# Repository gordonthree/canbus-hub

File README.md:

# CAN bus hub prototype

## CAN Hub
* eight total de9 connectors, one input, one output, six spurs
* each spur is wired in series, with Cx-IN and Cx-OUT daisy chained
* spurs that are not connected have a shorting plug installed connecting Cx-IN to Cx-OUT

## CAN Hub using pin-terminals
* six 6-position terminals wired in series
* each spur is wired in series, with Cx-IN and Cx-OUT daisy chained
* bus-power LED
* +12v and ground wired in parallel

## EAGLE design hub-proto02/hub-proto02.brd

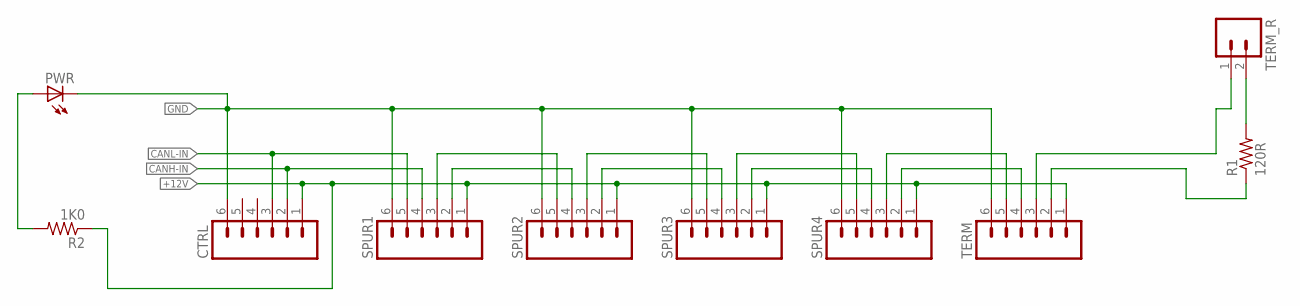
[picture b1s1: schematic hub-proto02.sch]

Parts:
CTRL: M06; 06P
PWR: LED3MM
R1: 120R; 0309/12
R2: 1K0; 0309/12
SPUR1, SPUR2, SPUR3, SPUR4: M06; 06P
TERM: M06; 06P
TERM_R: M02; 02P

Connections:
+12V: CTRL.1, R2.1, SPUR1.1, SPUR2.1, SPUR3.1, SPUR4.1, TERM.1
CANH-IN: CTRL.2, SPUR1.4
CANH-OUT: R1.1, TERM.2
CANL-IN: CTRL.3, SPUR1.5
CANL-OUT: TERM.3, TERM_R.1
GND: CTRL.6, PWR.K (C), SPUR1.6, SPUR2.6, SPUR3.6, SPUR4.6, TERM.6
unnamed: R1.2, TERM_R.2
unnamed: SPUR1.2, SPUR2.4
unnamed: SPUR1.3, SPUR2.5
unnamed: SPUR4.2, TERM.4
unnamed: SPUR4.3, TERM.5
unnamed: SPUR2.3, SPUR3.5
unnamed: SPUR2.2, SPUR3.4
unnamed: SPUR3.3, SPUR4.5
unnamed: SPUR3.2, SPUR4.4
unnamed: PWR.A, R2.2

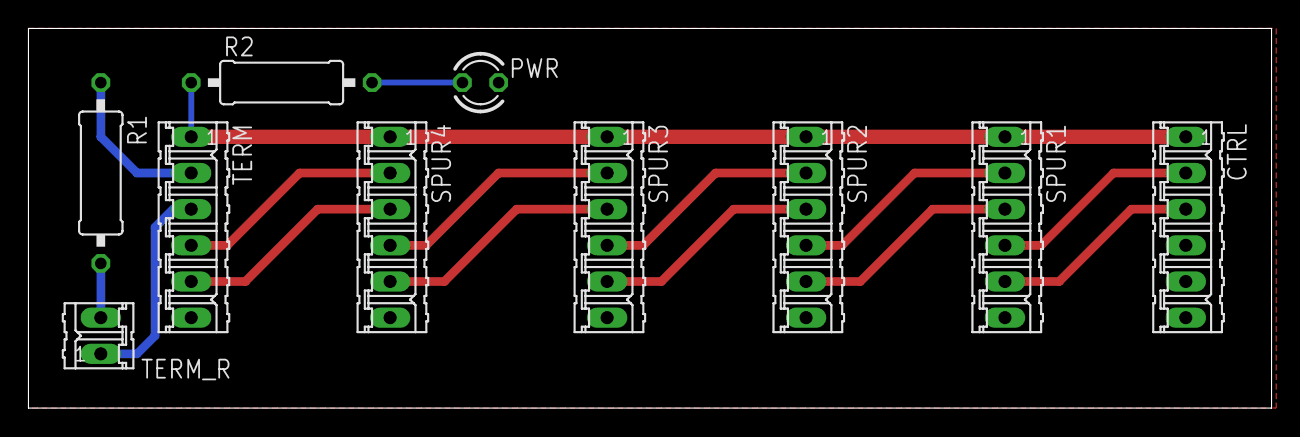
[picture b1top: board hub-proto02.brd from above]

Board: 2 copper layers, 87.3 x 26.7 mm, 10 parts (0 on the bottom side), 16 nets.

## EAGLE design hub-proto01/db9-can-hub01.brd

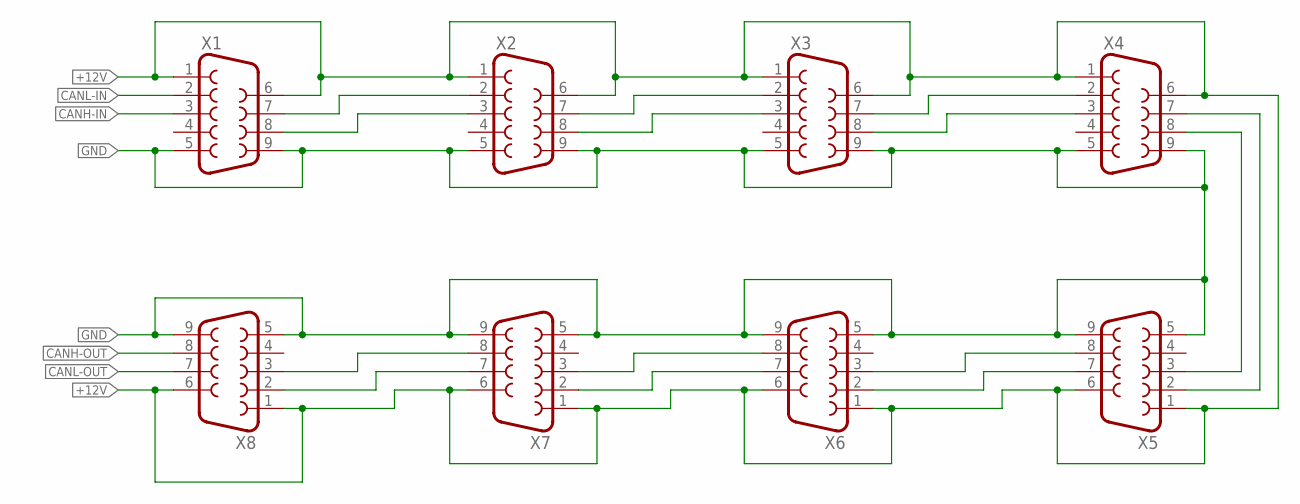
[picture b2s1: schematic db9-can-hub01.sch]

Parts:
X1, X2, X3, X4, X5, X6, X7, X8: F09H

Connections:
+12V: X1.1, X1.6, X2.1, X2.6, X3.1, X3.6, X4.1, X4.6, X5.1, X5.6, X6.1, X6.6, X7.1, X7.6, X8.1, X8.6
CANH-IN: X1.3
CANH-OUT: X8.8
CANL-IN: X1.2
CANL-OUT: X8.7
GND: X1.5, X1.9, X2.5, X2.9, X3.5, X3.9, X4.5, X4.9, X5.5, X5.9, X6.5, X6.9, X7.5, X7.9, X8.5, X8.9
unnamed: X1.7, X2.2
unnamed: X1.8, X2.3
unnamed: X2.7, X3.2
unnamed: X2.8, X3.3
unnamed: X3.7, X4.2
unnamed: X3.8, X4.3
unnamed: X4.8, X5.3
unnamed: X4.7, X5.2
unnamed: X5.7, X6.2
unnamed: X5.8, X6.3
unnamed: X6.7, X7.2
unnamed: X6.8, X7.3
unnamed: X7.7, X8.2
unnamed: X7.8, X8.3

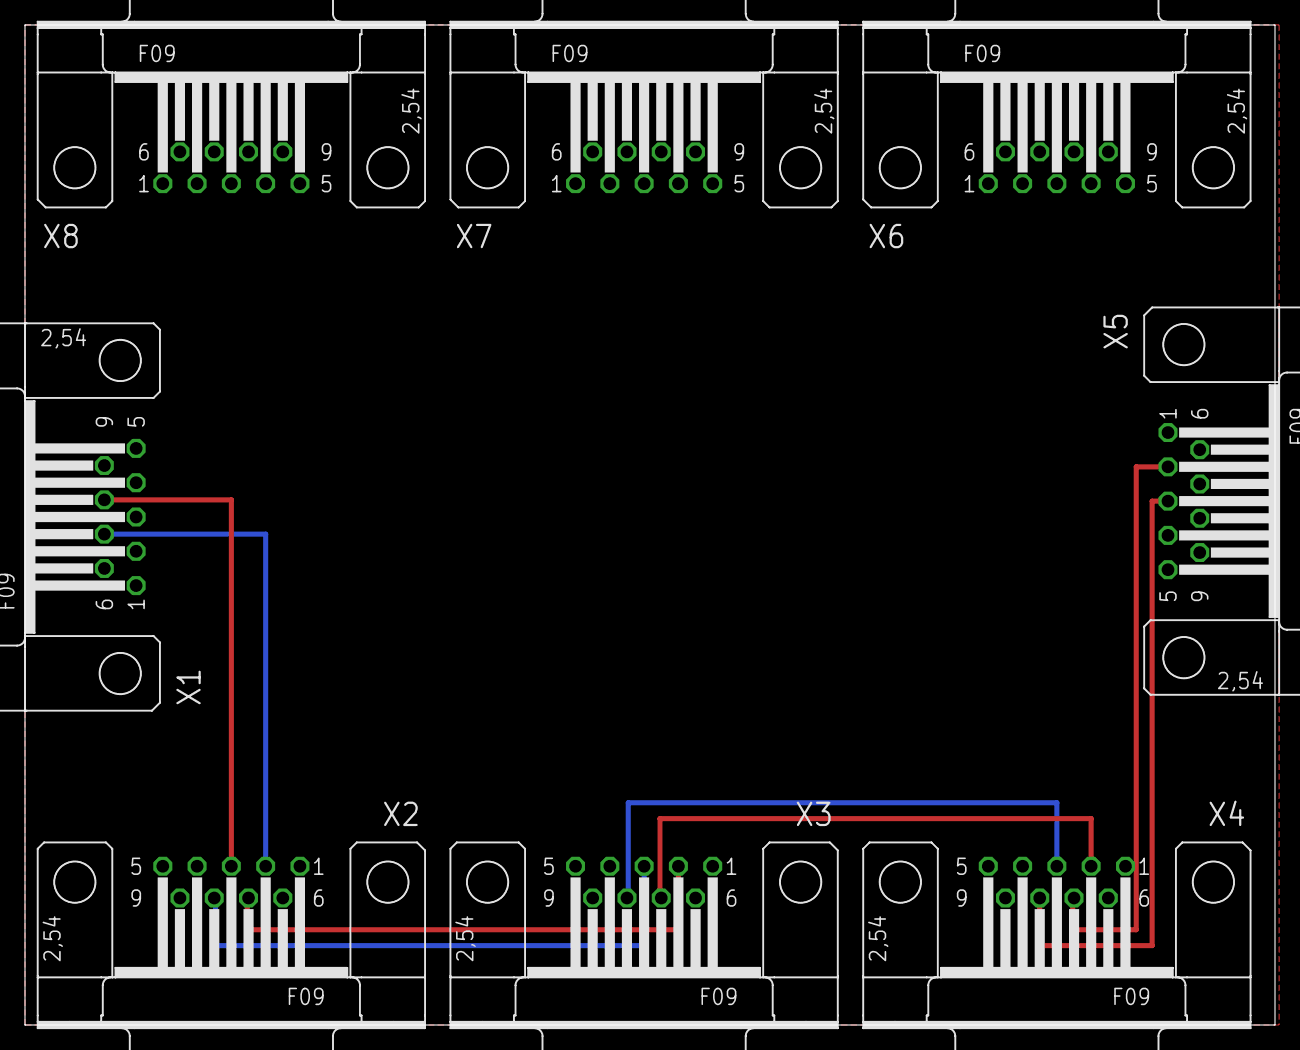
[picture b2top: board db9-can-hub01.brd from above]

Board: 2 copper layers, 100.0 x 80.0 mm, 8 parts (0 on the bottom side), 16 nets.

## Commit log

2025-04-21 hub prototypes
2025-04-21 refinement
2025-04-21 refinements
